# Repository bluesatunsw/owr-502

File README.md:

# owr
This repo includes all software necessary to operate the Test Rover Platform
that is being designed and developed in the OWR project.

## System Setup
A guide is available on the
[owr-docs](https://github.com/bluesatunsw/owr-docs/tree/main/src/guides/container_setup.md)
repository.

## Useful Command index
| Command                                                               | Effect                                                                                          |
| -------------------------------                                       | --------------------------------                                                                |
| `podman compose -f "$PWD/.devcontainer/docker-compose.yml" up -d`     | Run in the git root to build/restart/start the Docker container.                                |
| `podman compose -f "$PWD/.devcontainer/docker-compose-obc.yml" up -d` | Run in the git root to build/restart/start the Docker container **with obc specific settings!** |
| `podman exec -it --latest /bin/bash`                                  | Enter the docker container after launching it with the devcontainer.                            |
| `./utils/init.bash`                                                   | Run after `cd`'ing into `/workspaces/owr` in the container to source the ROS env and tools      |
| `colcon build --symlink-install`                                      | Runs the `colcon` meta build system, builds ALL rover packages!                                 |
| `ros2 launch rover rover.launch.py`                                   | Launch the robot state publisher. Just leave this running.                                      |
| `rqt`                                                                 | The flexible ROS2 viewer, useful for debugging topic flows and looking at raw topics.           |
| `rviz2`                                                               | Useful for visualizing TF2 / LiDAR / etc... data to see if it looks okay.                       |
| `podman rm --force --latest -t 0`                                     | Kill the podman container with the latest creation date (quickly)                               |

NOTE: `podman compose` will take a VERY long time! on uni Wi-Fi \~5min due to
the amount of packages it installs (\~5GB). There is also [a podman
bug](github.com/containers/podman/issues/16541) that invokes a postprocessing
step on the overlay filesystem, this will take **upwards of 10 minutes!** 

NOTE: `./utils/init.bash` will source the appropriate files as well as put you
in a 10-deep nested shell - running an invalid command will kill 1 level!

### Less Common Commands

| Command                                                               | Effect                                                                                    |
| -------------------------------                                       | --------------------------------                                                          |
| `ros2 launch rover rsp.launch.py`                                     | Robot State Publisher, publishes the URDF+JSP, to make it viewable in Lichtblick / Rviz2. |
| `xacro ./src/rover/description/robot.urdf.xacro > ./build/rover.urdf` | Compiles the xacro into a singular urdf file                                              |
| `ros2 run key_teleop key_teleop --ros-args -p twist_stamped_enabled:=True -r /key_vel:=/diff_drive_base_controller/cmd_vel` | Record keyboard imputs and publish them as Twist2d values, which ROS2Control is listening for!                              |

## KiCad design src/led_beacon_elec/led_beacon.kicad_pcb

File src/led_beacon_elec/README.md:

# LED Beacon

I've measured it to be around 155mm wide by 40mm tall

This is gonna cost around $29

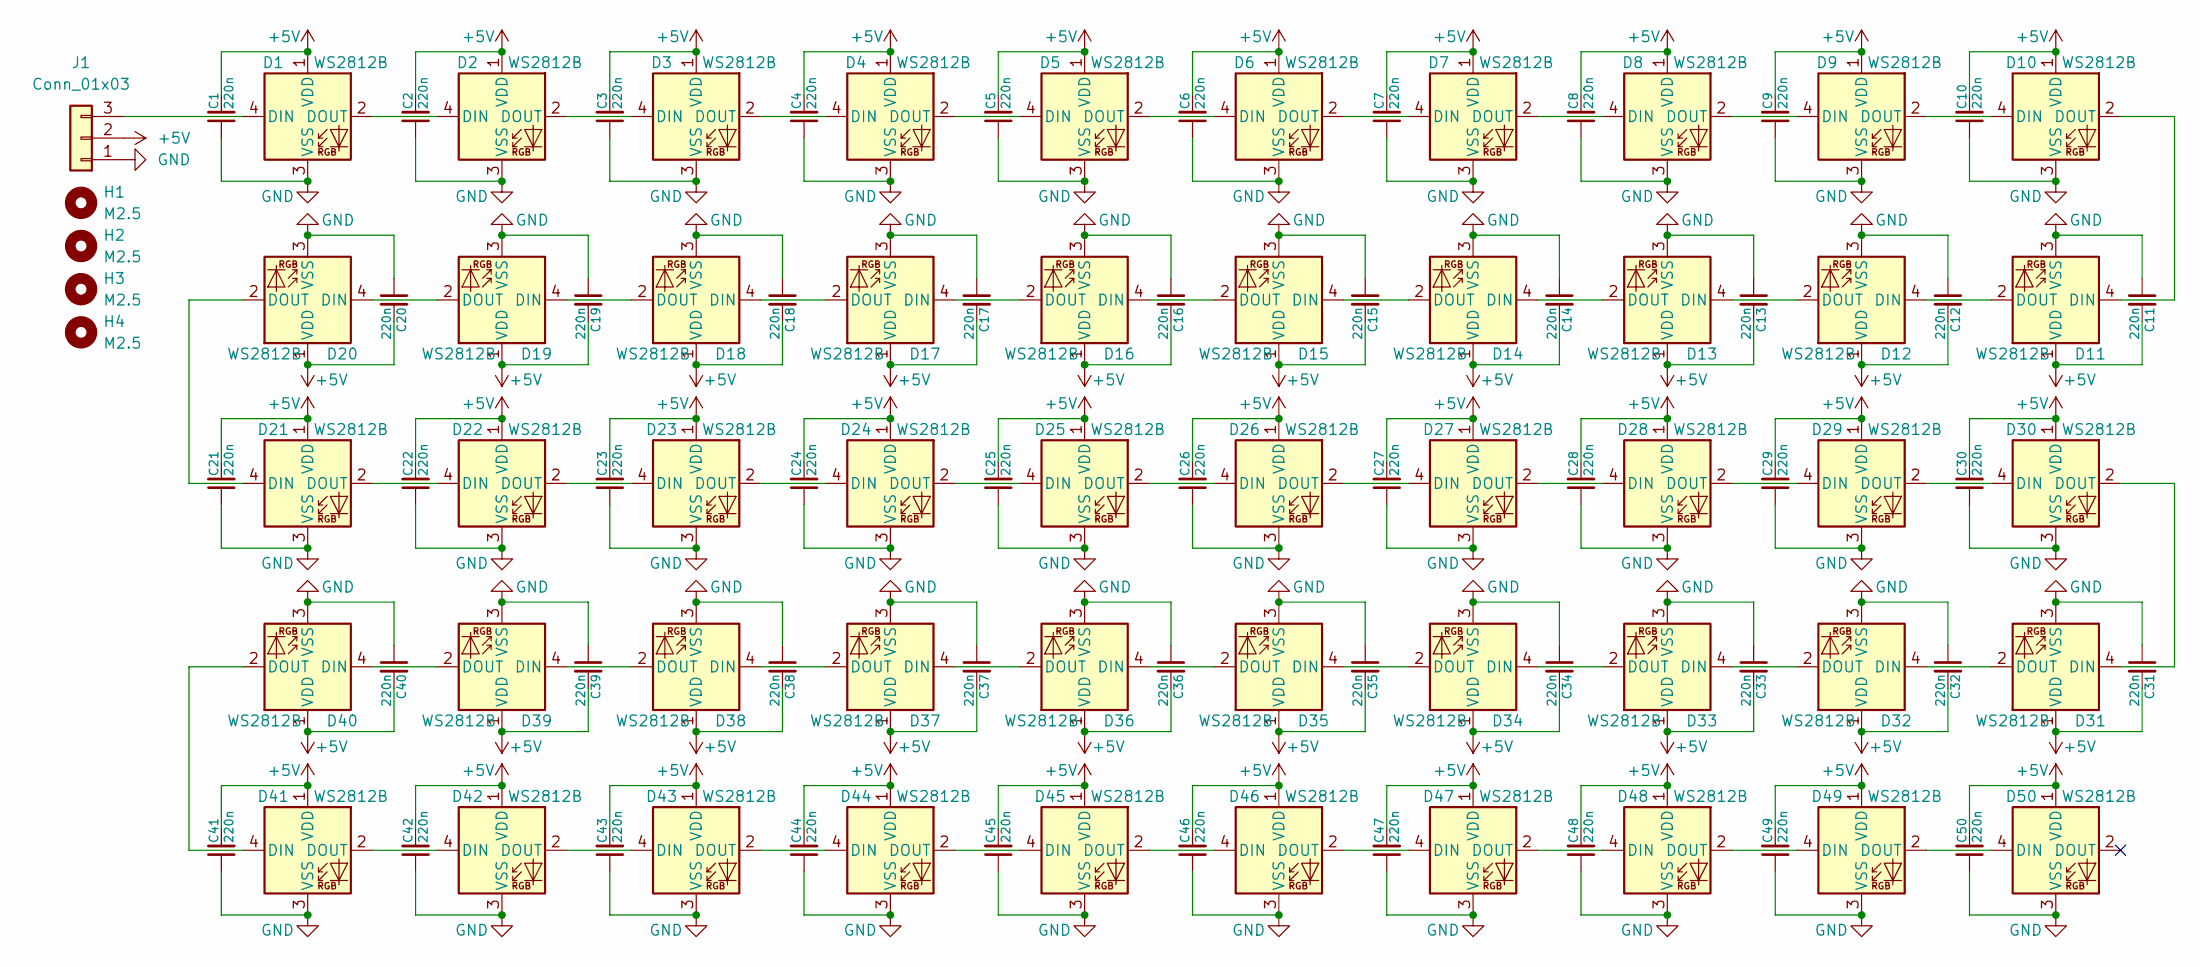
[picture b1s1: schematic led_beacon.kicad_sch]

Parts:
C1, C2, C3, C4, C5, C6, C7, C8, C9, C10, C11, C12, C13, C14, C15, C16, C17, C18, C19, C20, C21, C22, C23, C24, C25, C26, C27, C28, C29, C30, C31, C32, C33, C34, C35, C36, C37, C38, C39, C40, C41, C42, C43, C44, C45, C46, C47, C48, C49, C50: 220n; C_0402_1005Metric; Rating 10V
D1, D2, D3, D4, D5, D6, D7, D8, D9, D10, D11, D12, D13, D14, D15, D16, D17, D18, D19, D20, D21, D22, D23, D24, D25, D26, D27, D28, D29, D30, D31, D32, D33, D34, D35, D36, D37, D38, D39, D40, D41, D42, D43, D44, D45, D46, D47, D48, D49, D50: WS2812B; WS2812B-5050
H1, H2, H3, H4: M2.5; M2.5_Internal
J1: Conn_01x03; SM03B-PASS

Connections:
+5V: C1.2, C2.2, C3.2, C4.2, C5.2, C6.2, C7.2, C8.2, C9.2, C10.2, C11.2, C12.2, C13.2, C14.2, C15.2, C16.2, C17.2, C18.2, C19.2, C20.2, C21.2, C22.2, C23.2, C24.2, C25.2, C26.2, C27.2, C28.2, C29.2, C30.2, C31.2, C32.2, C33.2, C34.2, C35.2, C36.2, C37.2, C38.2, C39.2, C40.2, C41.2, C42.2, C43.2, C44.2, C45.2, C46.2, C47.2, C48.2, C49.2, C50.2, D1.1 (VDD), D2.1 (VDD), D3.1 (VDD), D4.1 (VDD), D5.1 (VDD), D6.1 (VDD), D7.1 (VDD), D8.1 (VDD), D9.1 (VDD), D10.1 (VDD), D11.1 (VDD), D12.1 (VDD), D13.1 (VDD), D14.1 (VDD), D15.1 (VDD), D16.1 (VDD), D17.1 (VDD), D18.1 (VDD), D19.1 (VDD), D20.1 (VDD), D21.1 (VDD), D22.1 (VDD), D23.1 (VDD), D24.1 (VDD), D25.1 (VDD), D26.1 (VDD), D27.1 (VDD), D28.1 (VDD), D29.1 (VDD), D30.1 (VDD), D31.1 (VDD), D32.1 (VDD), D33.1 (VDD), D34.1 (VDD), D35.1 (VDD), D36.1 (VDD), D37.1 (VDD), D38.1 (VDD), D39.1 (VDD), D40.1 (VDD), D41.1 (VDD), D42.1 (VDD), D43.1 (VDD), D44.1 (VDD), D45.1 (VDD), D46.1 (VDD), D47.1 (VDD), D48.1 (VDD), D49.1 (VDD), D50.1 (VDD), J1.2
GND: C1.1, C2.1, C3.1, C4.1, C5.1, C6.1, C7.1, C8.1, C9.1, C10.1, C11.1, C12.1, C13.1, C14.1, C15.1, C16.1, C17.1, C18.1, C19.1, C20.1, C21.1, C22.1, C23.1, C24.1, C25.1, C26.1, C27.1, C28.1, C29.1, C30.1, C31.1, C32.1, C33.1, C34.1, C35.1, C36.1, C37.1, C38.1, C39.1, C40.1, C41.1, C42.1, C43.1, C44.1, C45.1, C46.1, C47.1, C48.1, C49.1, C50.1, D1.3 (VSS), D2.3 (VSS), D3.3 (VSS), D4.3 (VSS), D5.3 (VSS), D6.3 (VSS), D7.3 (VSS), D8.3 (VSS), D9.3 (VSS), D10.3 (VSS), D11.3 (VSS), D12.3 (VSS), D13.3 (VSS), D14.3 (VSS), D15.3 (VSS), D16.3 (VSS), D17.3 (VSS), D18.3 (VSS), D19.3 (VSS), D20.3 (VSS), D21.3 (VSS), D22.3 (VSS), D23.3 (VSS), D24.3 (VSS), D25.3 (VSS), D26.3 (VSS), D27.3 (VSS), D28.3 (VSS), D29.3 (VSS), D30.3 (VSS), D31.3 (VSS), D32.3 (VSS), D33.3 (VSS), D34.3 (VSS), D35.3 (VSS), D36.3 (VSS), D37.3 (VSS), D38.3 (VSS), D39.3 (VSS), D40.3 (VSS), D41.3 (VSS), D42.3 (VSS), D43.3 (VSS), D44.3 (VSS), D45.3 (VSS), D46.3 (VSS), D47.3 (VSS), D48.3 (VSS), D49.3 (VSS), D50.3 (VSS), J1.1
unnamed: D1.4 (DIN), J1.3
unnamed: D1.2 (DOUT), D2.4 (DIN)
unnamed: D2.2 (DOUT), D3.4 (DIN)
unnamed: D3.2 (DOUT), D4.4 (DIN)
unnamed: D4.2 (DOUT), D5.4 (DIN)
unnamed: D5.2 (DOUT), D6.4 (DIN)
unnamed: D6.2 (DOUT), D7.4 (DIN)
unnamed: D7.2 (DOUT), D8.4 (DIN)
unnamed: D8.2 (DOUT), D9.4 (DIN)
unnamed: D9.2 (DOUT), D10.4 (DIN)
unnamed: D10.2 (DOUT), D11.4 (DIN)
unnamed: D11.2 (DOUT), D12.4 (DIN)
unnamed: D12.2 (DOUT), D13.4 (DIN)
unnamed: D13.2 (DOUT), D14.4 (DIN)
unnamed: D14.2 (DOUT), D15.4 (DIN)
unnamed: D15.2 (DOUT), D16.4 (DIN)
unnamed: D16.2 (DOUT), D17.4 (DIN)
unnamed: D17.2 (DOUT), D18.4 (DIN)
unnamed: D18.2 (DOUT), D19.4 (DIN)
unnamed: D19.2 (DOUT), D20.4 (DIN)
unnamed: D20.2 (DOUT), D21.4 (DIN)
unnamed: D21.2 (DOUT), D22.4 (DIN)
unnamed: D22.2 (DOUT), D23.4 (DIN)
unnamed: D23.2 (DOUT), D24.4 (DIN)
unnamed: D24.2 (DOUT), D25.4 (DIN)
unnamed: D25.2 (DOUT), D26.4 (DIN)
unnamed: D26.2 (DOUT), D27.4 (DIN)
unnamed: D27.2 (DOUT), D28.4 (DIN)
unnamed: D28.2 (DOUT), D29.4 (DIN)
unnamed: D29.2 (DOUT), D30.4 (DIN)
unnamed: D30.2 (DOUT), D31.4 (DIN)
unnamed: D31.2 (DOUT), D32.4 (DIN)
unnamed: D32.2 (DOUT), D33.4 (DIN)
unnamed: D33.2 (DOUT), D34.4 (DIN)
unnamed: D34.2 (DOUT), D35.4 (DIN)
unnamed: D35.2 (DOUT), D36.4 (DIN)
unnamed: D36.2 (DOUT), D37.4 (DIN)
unnamed: D37.2 (DOUT), D38.4 (DIN)
unnamed: D38.2 (DOUT), D39.4 (DIN)
unnamed: D39.2 (DOUT), D40.4 (DIN)
unnamed: D40.2 (DOUT), D41.4 (DIN)
unnamed: D41.2 (DOUT), D42.4 (DIN)
unnamed: D42.2 (DOUT), D43.4 (DIN)
unnamed: D43.2 (DOUT), D44.4 (DIN)
unnamed: D44.2 (DOUT), D45.4 (DIN)
unnamed: D45.2 (DOUT), D46.4 (DIN)
unnamed: D46.2 (DOUT), D47.4 (DIN)
unnamed: D47.2 (DOUT), D48.4 (DIN)
unnamed: D48.2 (DOUT), D49.4 (DIN)
unnamed: D49.2 (DOUT), D50.4 (DIN)

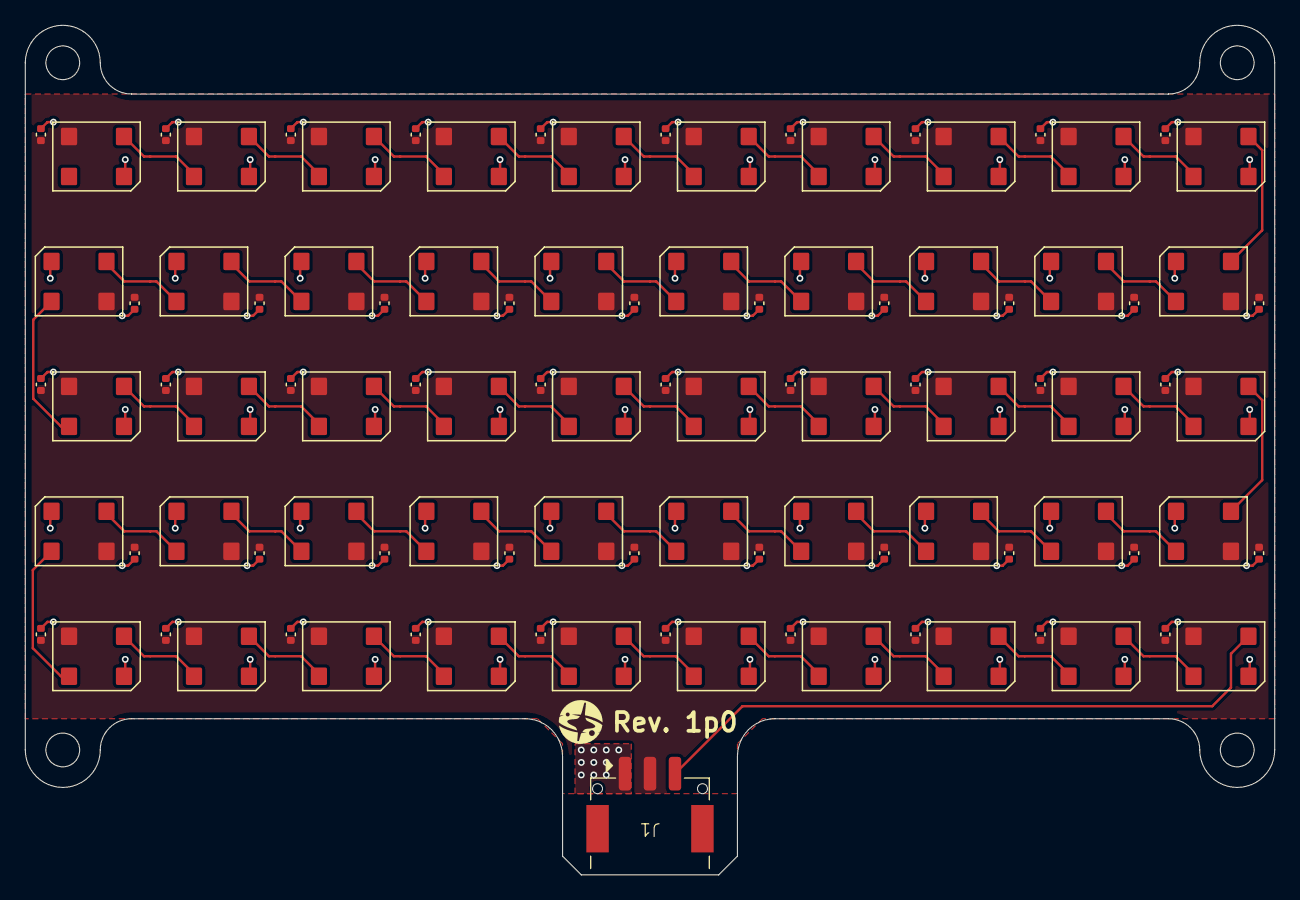
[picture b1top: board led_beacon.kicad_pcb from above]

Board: 2 copper layers, 100.0 x 68.0 mm, 105 parts (0 on the bottom side), 52 nets.

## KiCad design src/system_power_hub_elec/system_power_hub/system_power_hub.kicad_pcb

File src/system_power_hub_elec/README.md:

# System Power Hub (SPH)

Further distributes power from the MPH into eight channels. It complies with the common device specification 2025-04.

Power input for the MPH is provided via a male XT60 connector and each of the channel has a female XT30 power output connector.

## Switching
Power to each of the channels can be toggled by the MCU. When a channel is enabled, including when the device initially powers up, a soft start slowly reduces the output impedance to reduce inrush current. As implied by the connector name, each channel is able to output 30A peak and 20A continuous.

## Monitoring
The output current of each channel is monitored.

**[TODO] Explain how this will be implemented**

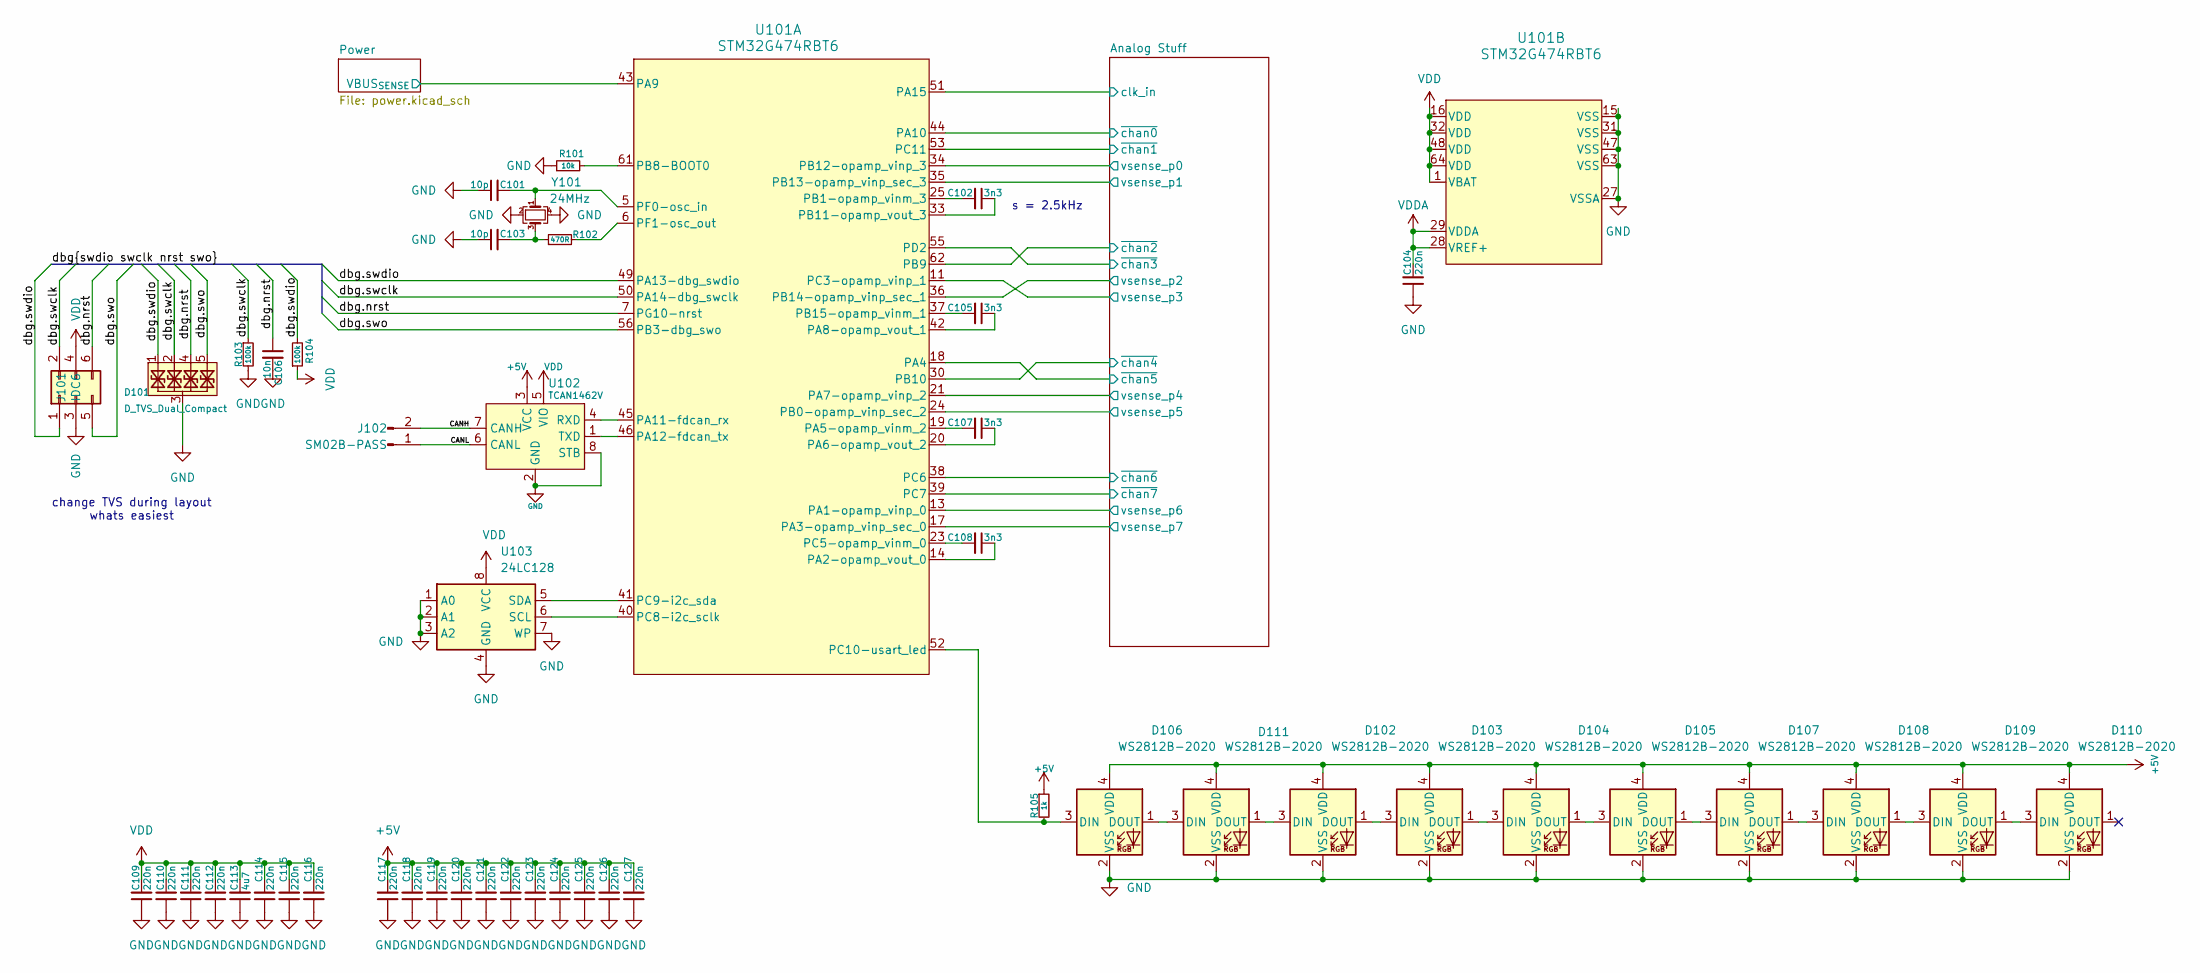
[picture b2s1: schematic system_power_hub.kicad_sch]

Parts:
C101, C103: 10p; C_0402_1005Metric
C102, C105, C107, C108: 3n3; C_0402_1005Metric
C104, C109, C110, C111, C112, C114, C115, C116, C117, C118, C119, C120, C121, C122, C123, C124, C125, C126, C127: 220n; C_0402_1005Metric
C106: 10n; C_0402_1005Metric
C113: 4u7; C_0805_2012Metric
D101: D_TVS_Dual_Compact; Diodes_UDFN-10_1x2.5mm_P0.5mm
D102, D103, D104, D105, D106, D107, D108, D109, D110, D111: WS2812B-2020
J101: IDC6
J102: SM02B-PASS
R101: 10k; R_0402_1005Metric
R102: 470R; R_0402_1005Metric
R103, R104: 100k; R_0402_1005Metric
R105: 1k; R_0402_1005Metric
U101: STM32G474RBT6; LQFP-64-0.5
U102: TCAN1462V; SOIC-8_3.9x4.9mm_P1.27mm
U103: 24LC128; TSSOP-8_4.4x3mm_P0.65mm
Y101: 24MHz; Crystal_SMD_2016-4Pin_2.0x1.6mm

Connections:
+5V: C117.2, C118.2, C119.2, C120.2, C121.2, C122.2, C123.2, C124.2, C125.2, C126.2, C127.2, D102.4 (VDD), D103.4 (VDD), D104.4 (VDD), D105.4 (VDD), D106.4 (VDD), D107.4 (VDD), D108.4 (VDD), D109.4 (VDD), D110.4 (VDD), D111.4 (VDD), R105.1, U102.3 (VCC); also elsewhere on the board
/Analog Stuff/clk_in: U101.51 (PA15); also elsewhere on the board
/Analog Stuff/vsense_p0: U101.34 (PB12-opamp_vinp_3); also elsewhere on the board
/Analog Stuff/vsense_p1: U101.35 (PB13-opamp_vinp_sec_3); also elsewhere on the board
/Analog Stuff/vsense_p2: U101.36 (PB14-opamp_vinp_sec_1); also elsewhere on the board
/Analog Stuff/vsense_p3: U101.11 (PC3-opamp_vinp_1); also elsewhere on the board
/Analog Stuff/vsense_p4: U101.21 (PA7-opamp_vinp_2); also elsewhere on the board
/Analog Stuff/vsense_p5: U101.24 (PB0-opamp_vinp_sec_2); also elsewhere on the board
/Analog Stuff/vsense_p6: U101.13 (PA1-opamp_vinp_0); also elsewhere on the board
/Analog Stuff/vsense_p7: U101.17 (PA3-opamp_vinp_sec_0); also elsewhere on the board
/Analog Stuff/~chan0: U101.44 (PA10); also elsewhere on the board
/Analog Stuff/~chan1: U101.53 (PC11); also elsewhere on the board
/Analog Stuff/~chan2: U101.62 (PB9); also elsewhere on the board
/Analog Stuff/~chan3: U101.55 (PD2); also elsewhere on the board
/Analog Stuff/~chan4: U101.30 (PB10); also elsewhere on the board
/Analog Stuff/~chan5: U101.18 (PA4); also elsewhere on the board
/Analog Stuff/~chan6: U101.38 (PC6); also elsewhere on the board
/Analog Stuff/~chan7: U101.39 (PC7); also elsewhere on the board
/CANH: J102.2, U102.7 (CANH)
/CANL: J102.1, U102.6 (CANL)
/Power/VBUS_{SENSE}: U101.43 (PA9); also elsewhere on the board
/dbg.nrst: C106.1, D101.4, D101.7, J101.6, U101.7 (PG10-nrst)
/dbg.swclk: D101.2, D101.9, J101.2, R103.1, U101.50 (PA14-dbg_swclk)
/dbg.swdio: D101.1, D101.10, J101.1, R104.2, U101.49 (PA13-dbg_swdio)
/dbg.swo: D101.5, D101.6, J101.5, U101.56 (PB3-dbg_swo)
GND: C101.1, C103.1, C104.1, C106.2, C109.1, C110.1, C111.1, C112.1, C113.1, C114.1, C115.1, C116.1, C117.1, C118.1, C119.1, C120.1, C121.1, C122.1, C123.1, C124.1, C125.1, C126.1, C127.1, D101.3, D101.8, D102.2 (VSS), D103.2 (VSS), D104.2 (VSS), D105.2 (VSS), D106.2 (VSS), D107.2 (VSS), D108.2 (VSS), D109.2 (VSS), D110.2 (VSS), D111.2 (VSS), J101.3, R101.1, R103.2, U101.15 (VSS), U101.27 (VSSA), U101.31 (VSS), U101.47 (VSS), U101.63 (VSS), U102.2 (GND), U102.8 (STB), U102.9 (EP), U103.1 (A0), U103.2 (A1), U103.3 (A2), U103.4 (GND), U103.7 (WP), Y101.2, Y101.4; also elsewhere on the board
unnamed: C103.2, R102.1, Y101.3
unnamed: D102.3 (DIN), D111.1 (DOUT)
unnamed: D102.1 (DOUT), D103.3 (DIN)
unnamed: D103.1 (DOUT), D104.3 (DIN)
unnamed: D104.1 (DOUT), D105.3 (DIN)
unnamed: D105.1 (DOUT), D107.3 (DIN)
unnamed: D106.3 (DIN), R105.2, U101.52 (PC10-usart_led)
unnamed: D106.1 (DOUT), D111.3 (DIN)
unnamed: D107.1 (DOUT), D108.3 (DIN)
unnamed: D108.1 (DOUT), D109.3 (DIN)
unnamed: D109.1 (DOUT), D110.3 (DIN)
unnamed: C108.1, U101.14 (PA2-opamp_vout_0)
unnamed: C107.2, U101.19 (PA5-opamp_vinm_2)
unnamed: C107.1, U101.20 (PA6-opamp_vout_2)
unnamed: C105.1, U101.42 (PA8-opamp_vout_1)
unnamed: U101.45 (PA11-fdcan_rx), U102.4 (RXD)
unnamed: U101.46 (PA12-fdcan_tx), U102.1 (TXD)
unnamed: C102.2, U101.25 (PB1-opamp_vinm_3)
unnamed: R101.2, U101.61 (PB8-BOOT0)
unnamed: C102.1, U101.33 (PB11-opamp_vout_3)
unnamed: C105.2, U101.37 (PB15-opamp_vinm_1)
unnamed: C108.2, U101.23 (PC5-opamp_vinm_0)
unnamed: U101.40 (PC8-i2c_sclk), U103.6 (SCL)
unnamed: U101.41 (PC9-i2c_sda), U103.5 (SDA)
unnamed: C101.2, U101.5 (PF0-osc_in), Y101.1
unnamed: R102.2, U101.6 (PF1-osc_out)
VDD: C109.2, C110.2, C111.2, C112.2, C113.2, C114.2, C115.2, C116.2, J101.4, R104.1, U101.1 (VBAT), U101.16 (VDD), U101.32 (VDD), U101.48 (VDD), U101.64 (VDD), U102.5 (VIO), U103.8 (VCC); also elsewhere on the board
VDDA: C104.2, U101.28 (VREF+), U101.29 (VDDA); also elsewhere on the board

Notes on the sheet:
s = 2.5kHz
change TVS during layout whats easiest

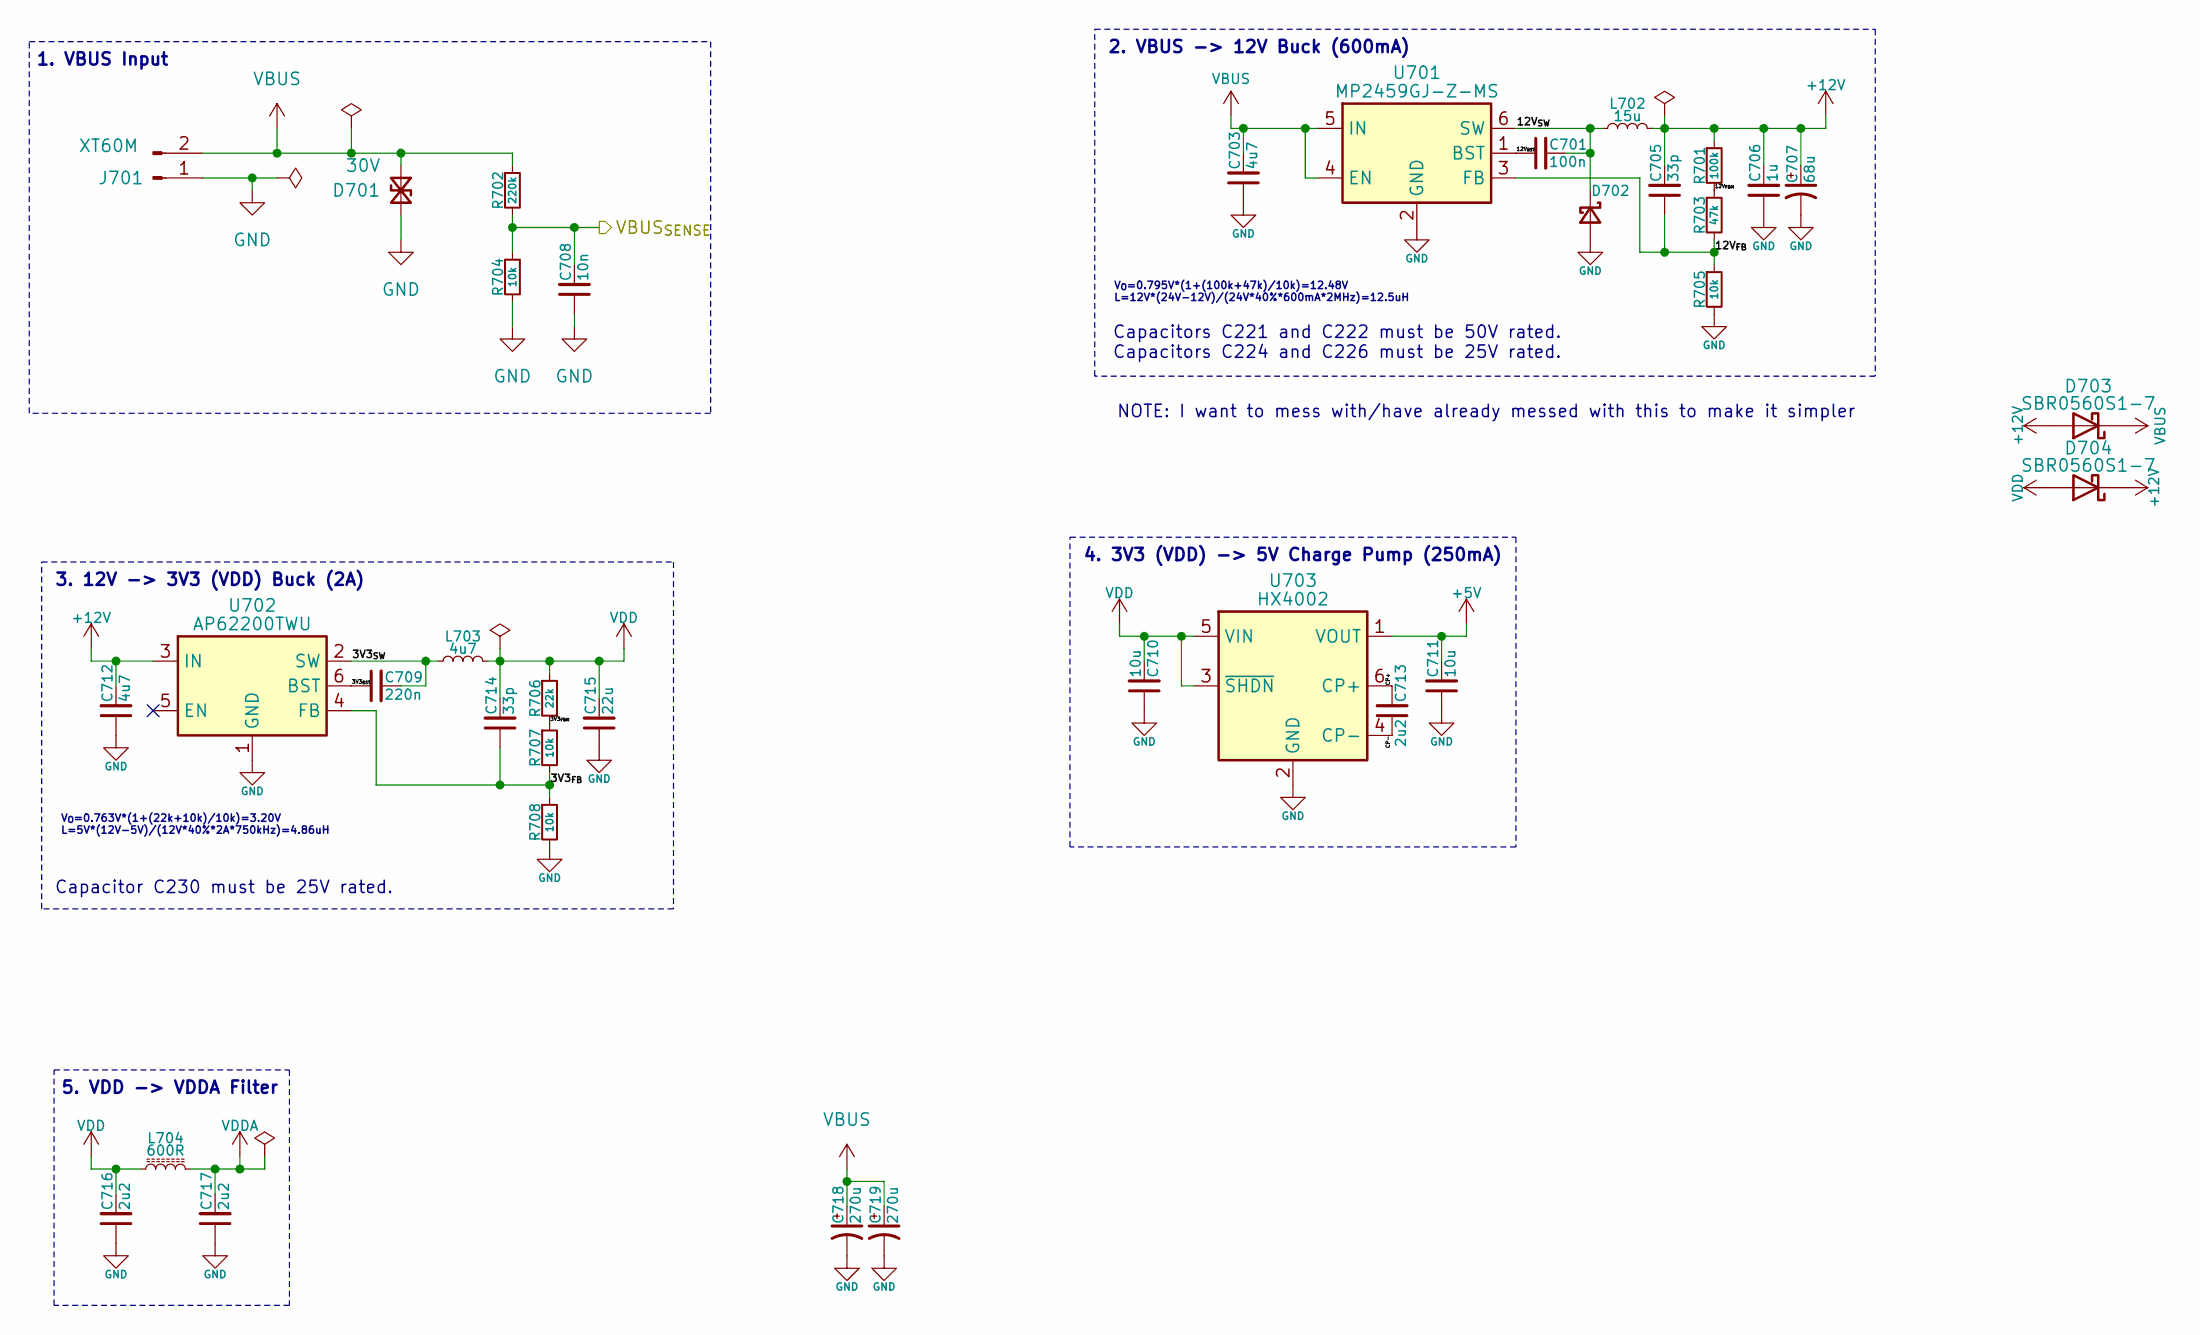
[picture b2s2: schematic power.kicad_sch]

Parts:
C701: 100n; C_0402_1005Metric
C703: 4u7; C_1210_3225Metric
C705, C714: 33p; C_0402_1005Metric
C706: 1u; C_0805_2012Metric
C707: 68u; CP_Elec_6.3x7.7
C708: 10n; C_0402_1005Metric
C709: 220n; C_0402_1005Metric
C710, C711: 10u; C_1206_3216Metric
C712: 4u7; C_1206_3216Metric
C713, C716, C717: 2u2; C_0603_1608Metric
C715: 22u; C_1210_3225Metric
C718, C719: 270u; CP_Elec_10x10
D701: 30V; D_SMF
D702: D_Schottky_Small; D_SOD-123
D703, D704: SBR0560S1-7; D_SOD-882
J701: XT60M; AMASS_XT60PW-M_1x02_P7.20mm_Horizontal
L702: 15u; L_Changjiang_FNR5040S
L703: 4u7; L_Changjiang_FNR4020S
L704: 600R; R_0402_1005Metric
R701: 100k; R_0402_1005Metric
R702: 220k; R_0402_1005Metric
R703: 47k; R_0402_1005Metric
R704, R705, R707, R708: 10k; R_0402_1005Metric
R706: 22k; R_0402_1005Metric
U701: MP2459GJ-Z-MS; TSOT-23-6
U702: AP62200TWU; TSOT-23-6
U703: HX4002; SOT-23-6

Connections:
+5V: C711.2, U703.1 (VOUT); also elsewhere on the board
+12V: C705.2, C706.2, C707.1, C712.2, D703.2 (A), D704.1 (K), L702.1, R701.1, U702.3 (IN); also elsewhere on the board
/Power/3V3_{BST}: C709.1, U702.6 (BST)
/Power/3V3_{FBM}: R706.2, R707.1
/Power/3V3_{FB}: C714.1, R707.2, R708.1, U702.4 (FB)
/Power/3V3_{SW}: C709.2, L703.1, U702.2 (SW)
/Power/12V_{BST}: C701.1, U701.1 (BST)
/Power/12V_{FBM}: R701.2, R703.1
/Power/12V_{FB}: C705.1, R703.2, R705.1, U701.3 (FB)
/Power/12V_{SW}: C701.2, D702.1 (K), L702.2, U701.6 (SW)
/Power/CP+: C713.2, U703.6 (CP+)
/Power/CP-: C713.1, U703.4 (CP-)
/Power/VBUS_{SENSE}: C708.2, R702.2, R704.1; also elsewhere on the board
GND: C703.1, C706.1, C707.2, C708.1, C710.1, C711.1, C712.1, C715.1, C716.1, C717.1, C718.2, C719.2, D701.2 (A2), D702.2 (A), J701.1, R704.2, R705.2, R708.2, U701.2 (GND), U702.1 (GND), U703.2 (GND); also elsewhere on the board
VBUS: C703.2, C718.1, C719.1, D701.1 (A1), D703.1 (K), J701.2, R702.1, U701.4 (EN), U701.5 (IN); also elsewhere on the board
VDD: C710.2, C714.2, C715.2, C716.2, D704.2 (A), L703.2, L704.1, R706.1, U703.3 (~SHDN), U703.5 (VIN); also elsewhere on the board
VDDA: C717.2, L704.2; also elsewhere on the board

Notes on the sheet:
4. 3V3 (VDD) -> 5V Charge Pump (250mA)
Capacitor C230 must be 25V rated.
1. VBUS Input
V_{O}=0.795V*(1+(100k+47k)/10k)=12.48V L=12V*(24V-12V)/(24V*40%*600mA*2MHz)=12.5uH
2. VBUS -> 12V Buck (600mA)
Capacitors C221 and C222 must be 50V rated. Capacitors C224 and C226 must be 25V rated.
NOTE: I want to mess with/have already messed with this to make it simpler
5. VDD -> VDDA Filter
3. 12V -> 3V3 (VDD) Buck (2A)
V_{O}=0.763V*(1+(22k+10k)/10k)=3.20V L=5V*(12V-5V)/(12V*40%*2A*750kHz)=4.86uH

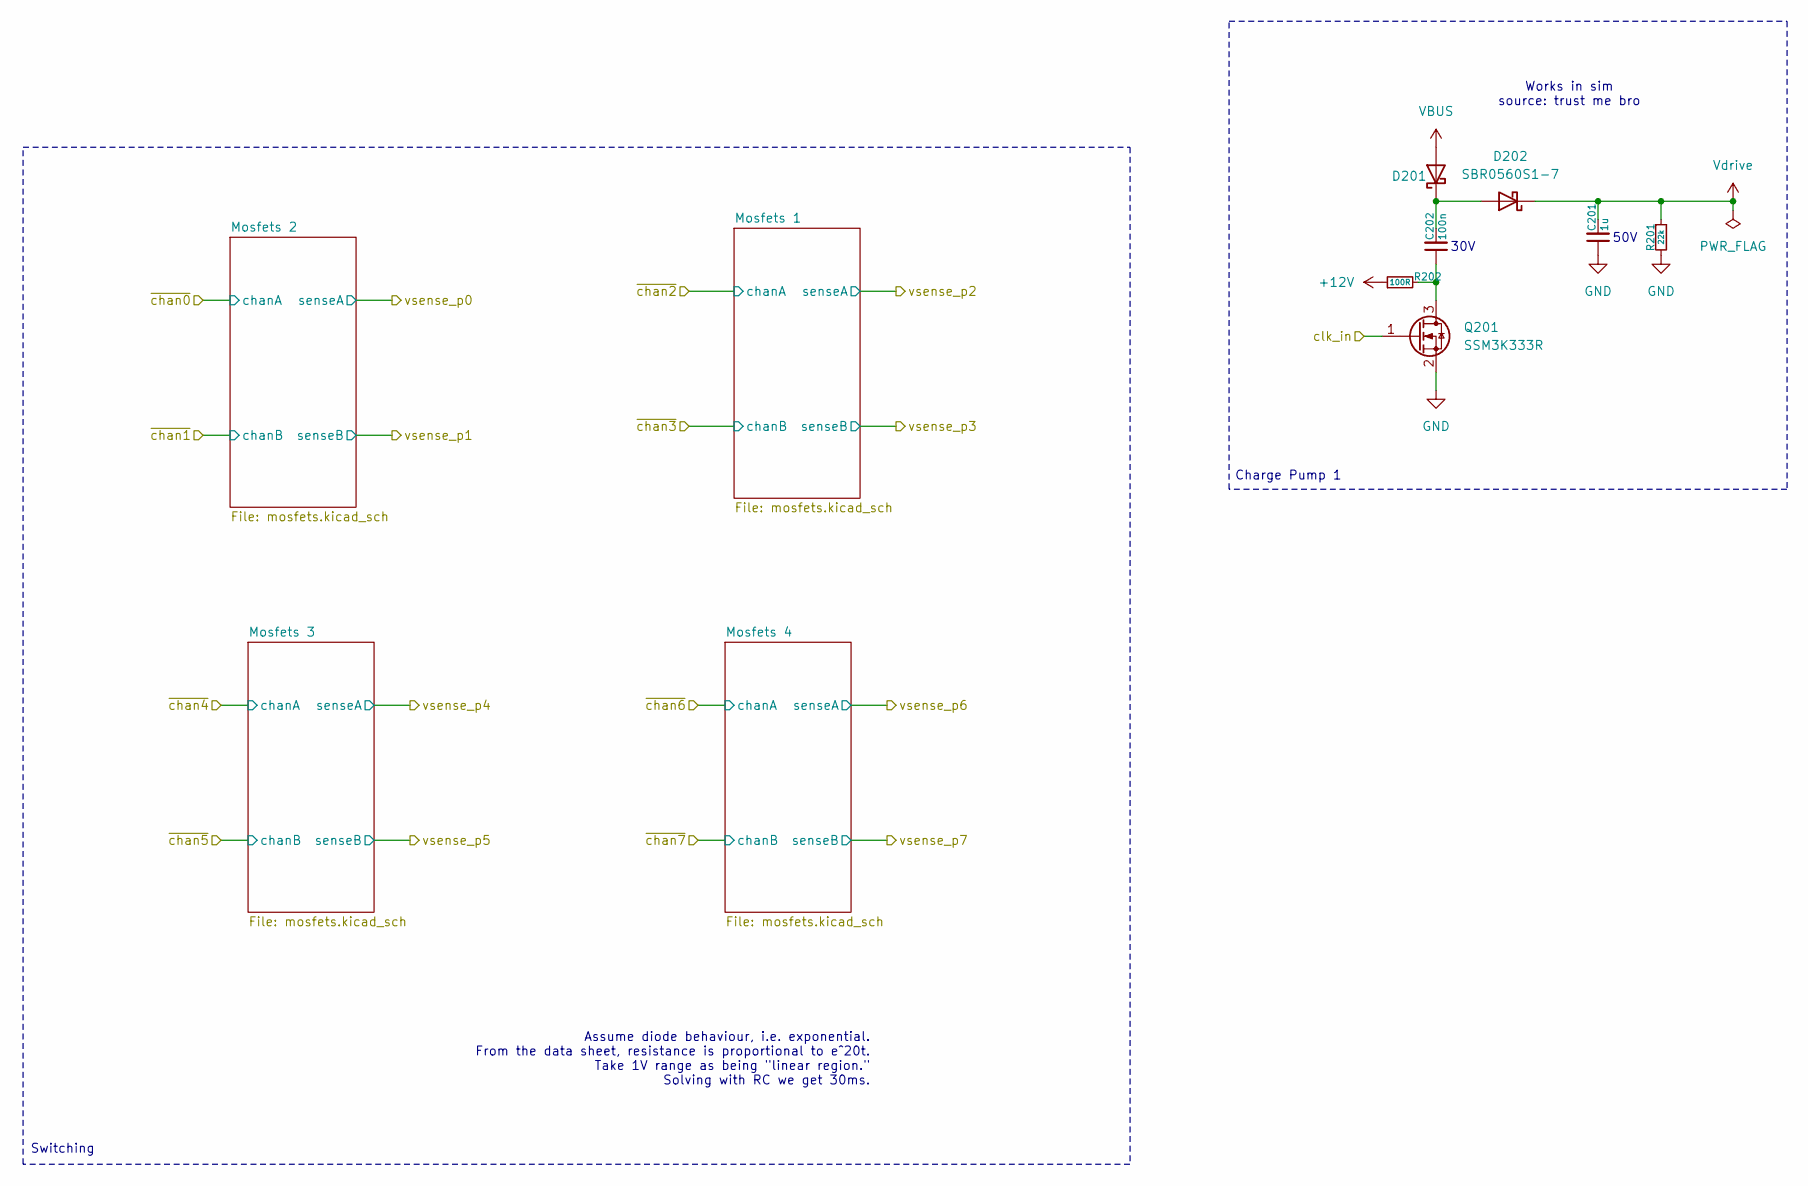
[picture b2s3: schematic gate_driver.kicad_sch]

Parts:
C201: 1u; C_1206_3216Metric
C202: 100n; C_0603_1608Metric
D201, D202: SBR0560S1-7; D_SOD-882
Q201: SSM3K333R; SOT-23-3
R201: 22k; R_0402_1005Metric
R202: 100R; R_0402_1005Metric

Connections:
+12V: R202.1; also elsewhere on the board
/Analog Stuff/clk_in: Q201.1 (G); also elsewhere on the board
GND: C201.1, Q201.2 (S), R201.2; also elsewhere on the board
unnamed: C202.2, D201.1 (K), D202.2 (A)
unnamed: C202.1, Q201.3 (D), R202.2
VBUS: D201.2 (A); also elsewhere on the board
Vdrive: C201.2, D202.1 (K), R201.1; also elsewhere on the board

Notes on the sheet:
Switching
50V
Charge Pump 1
Assume diode behaviour, i.e. exponential. From the data sheet, resistance is proportional to e^20t. Take 1V range as being "linear region." Solving with RC we get 30ms.
Works in sim source: trust me bro
30V
